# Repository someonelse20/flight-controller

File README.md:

# Custom Flight Controller

A custom flight controller with IMU sensors for orientation, a GPS module, a Micro SD card slot, and support for my LoRa Transceiver module for telemetry along with a custom flight controller algorithm.
I built this for my project of creating a custom drone from scratch. 

## Usage
To use plug in a 3 cell lipo battery into the XT60 connector and attach the ESCs to the 4 corner screw terminals. Then plug in the ESC headers into the coresponding ESC headers on the board. 
Make sure a GPS antenna is connected to the U.FL connector. Plug in my transceiver module into any of the UART headers.
A Micro SD card is not strictly required but if inserted the board will log data and error logs. 

## Project Images

## BOM
The full BOM from digikey is in the digikey-bom.csv file in production.

| PCB Assembly        | JLCPCB  | 96.10 | https://jlcpcb.com                                 |
|---------------------|---------|-------|----------------------------------------------------|
| Hand Soldered Parts | Digikey | 67.30 | https://www.digikey.com/en/mylists/list/OHMGL71TDV |

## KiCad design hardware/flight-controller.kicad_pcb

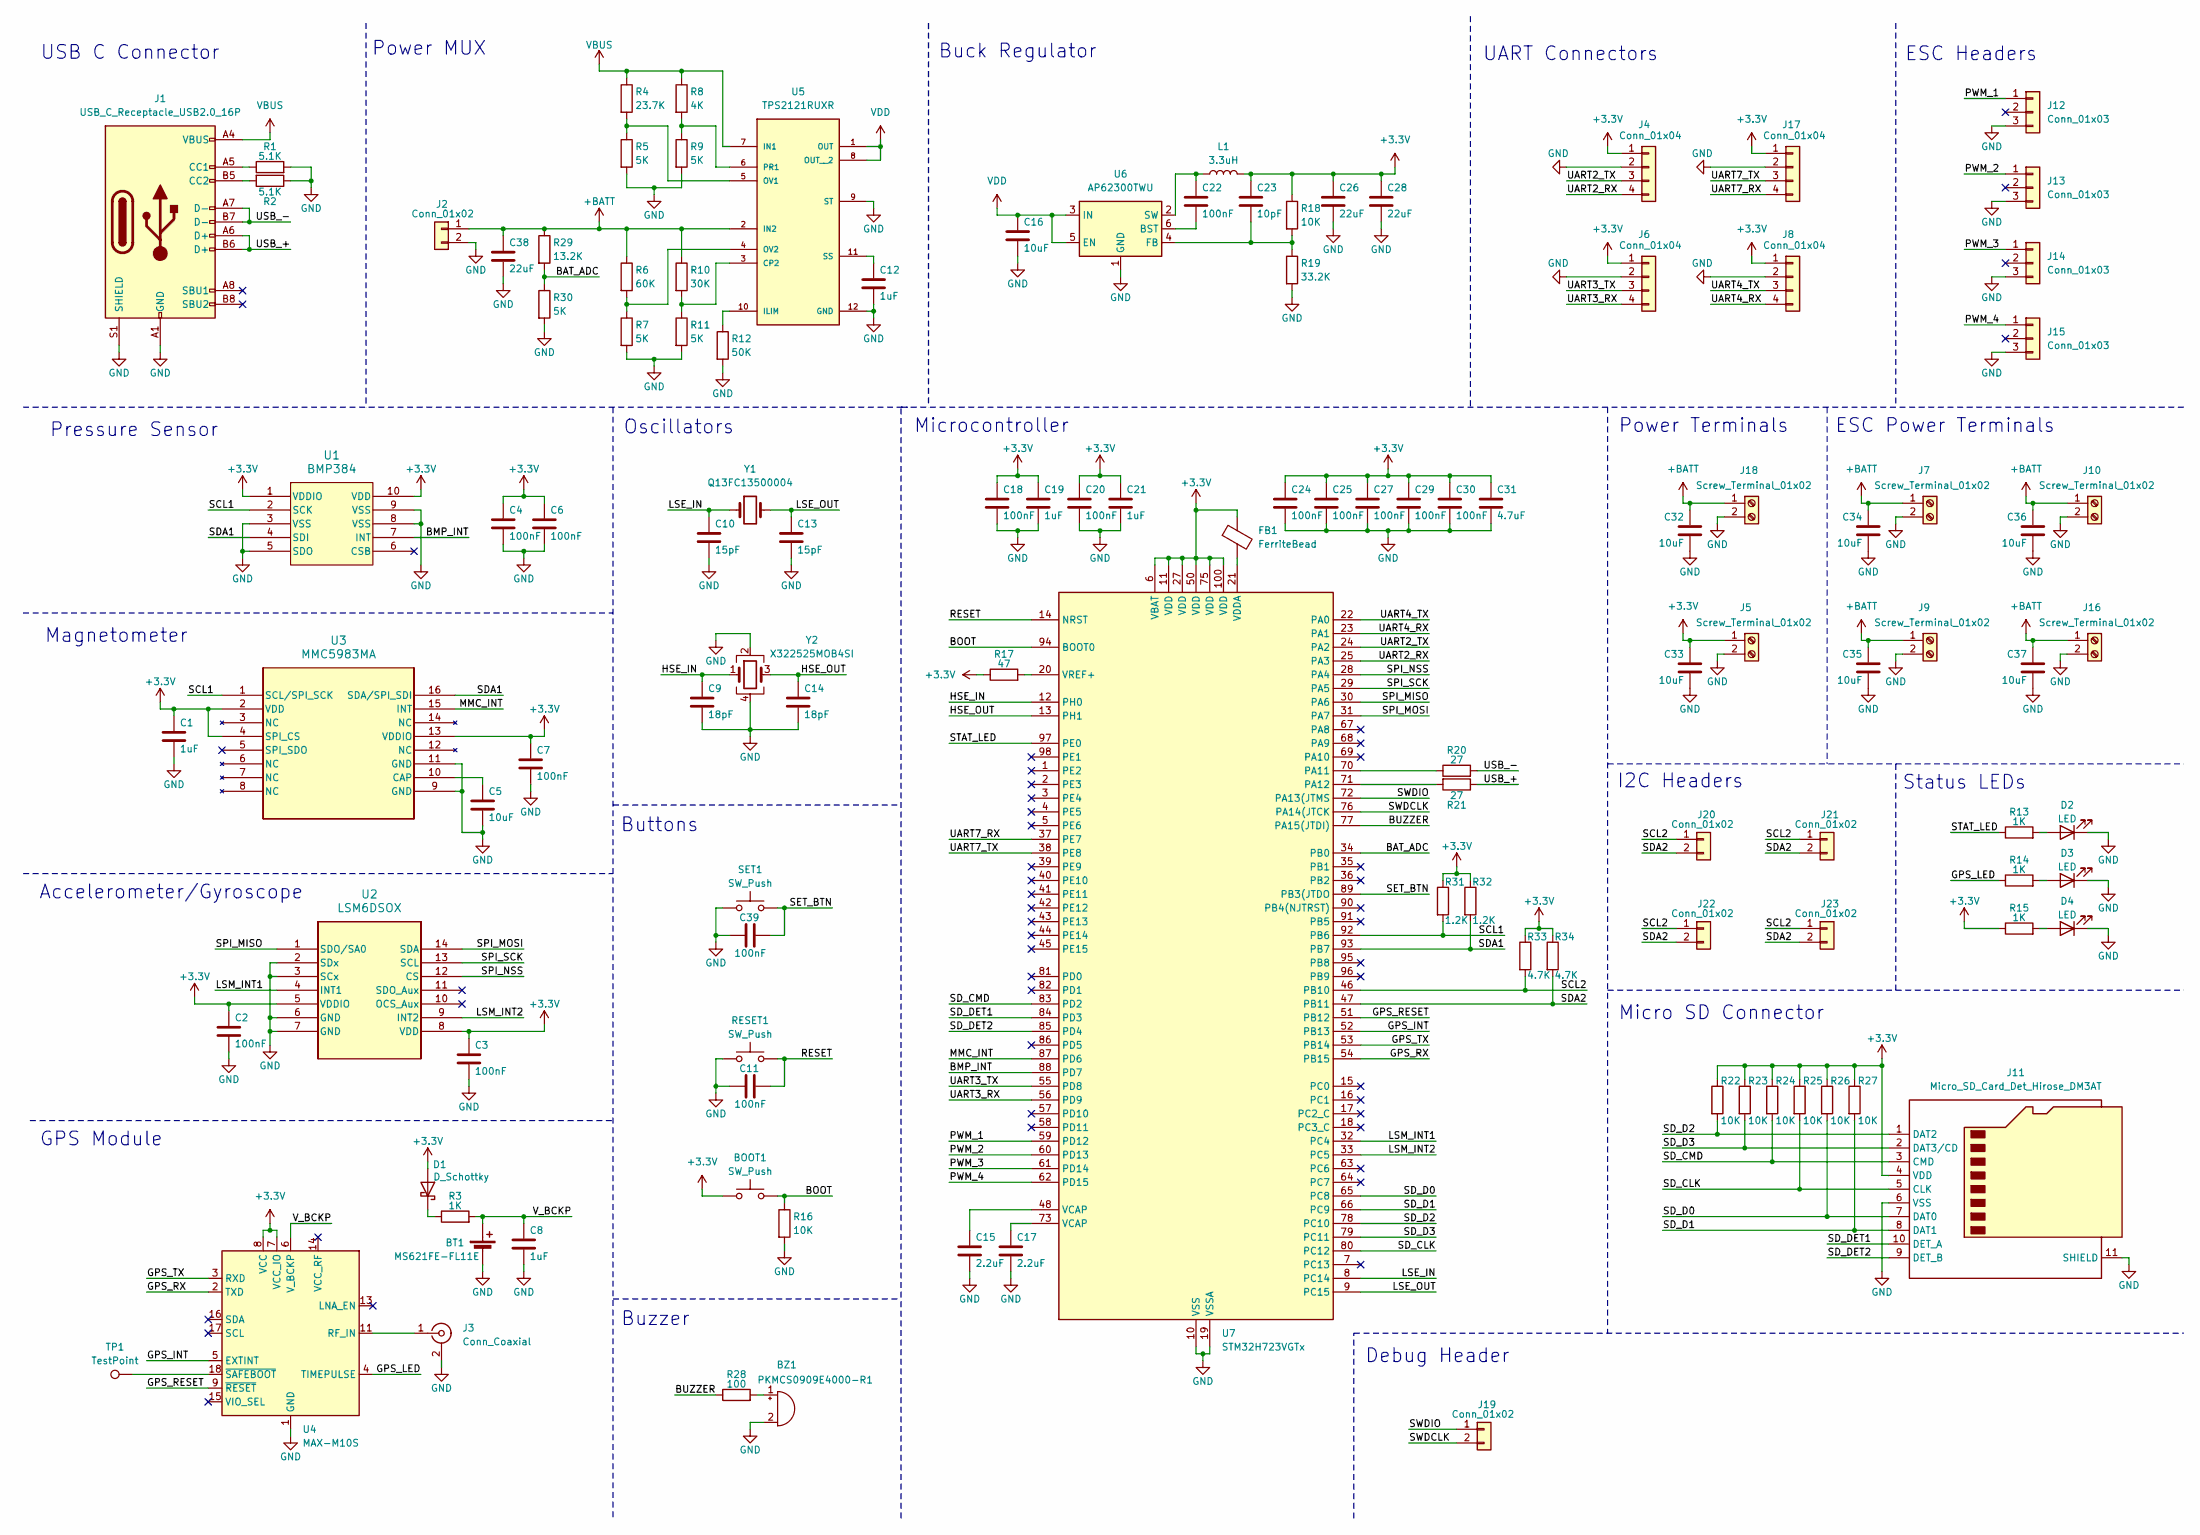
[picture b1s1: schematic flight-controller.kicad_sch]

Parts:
BOOT1: SW_Push; SW_Push_SPST_NO_Alps_SKRK
BT1: MS621FE-FL11E; BAT_MS621FE-FL11E
BZ1: PKMCS0909E4000-R1; SPKR_PKMCS0909E4000-R1
C1, C8, C19, C21: 1uF; C_0603_1608Metric
C2, C3, C4, C6, C7, C11, C18, C20, C22, C24, C25, C27, C29, C30, C39: 100nF; C_0402_1005Metric
C5, C16: 10uF; C_0603_1608Metric
C9, C14: 18pF; C_0402_1005Metric
C10, C13: 15pF; C_0402_1005Metric
C12: 1uF; C_0402_1005Metric
C15, C17: 2.2uF; C_0402_1005Metric
C23: 10pF; C_0402_1005Metric
C26, C28: 22uF; C_0603_1608Metric
C31: 4.7uF; C_0603_1608Metric
C32, C33, C34, C35, C36, C37: 10uF; C_0805_2012Metric
C38: 22uF; C_1206_3216Metric
D1: D_Schottky; D_0603_1608Metric
D2, D3, D4: LED; LED_0603_1608Metric
FB1: FerriteBead; L_0603_1608Metric
J1: USB_C_Receptacle_USB2.0_16P; USB_C_Receptacle_GCT_USB4105-xx-A_16P_TopMnt_Horizontal
J2: Conn_01x02; AMASS_XT60-M_1x02_P7.20mm_Vertical
J3: Conn_Coaxial; U.FL_Molex_MCRF_73412-0110_Vertical
J4, J6, J8, J17: Conn_01x04; JST_XH_B4B-XH-A_1x04_P2.50mm_Vertical
J5, J7, J9, J10, J16, J18: Screw_Terminal_01x02; TerminalBlock_MaiXu_MX126-5.0-02P_1x02_P5.00mm
J11: Micro_SD_Card_Det_Hirose_DM3AT; microSD_HC_Hirose_DM3AT-SF-PEJM5
J12, J13, J14, J15: Conn_01x03; PinHeader_1x03_P2.54mm_Vertical
J19, J20, J21, J22, J23: Conn_01x02; PinHeader_1x02_P2.54mm_Vertical
L1: 3.3uH; IND_SRP4030FA_BRN
R1, R2: 5.1K; R_0402_1005Metric
R3, R13, R14, R15: 1K; R_0402_1005Metric
R4: 23.7K; R_0402_1005Metric
R5, R7, R9, R11, R30: 5K; R_0402_1005Metric
R6: 60K; R_0603_1608Metric
R8: 4K; R_0603_1608Metric
R10: 30K; R_0402_1005Metric
R12: 50K; R_0603_1608Metric
R16, R18, R22, R23, R24, R25, R26, R27: 10K; R_0402_1005Metric
R17: 47; R_0402_1005Metric
R19: 33.2K; R_0402_1005Metric
R20, R21: 27; R_0402_1005Metric
R28: 100; R_0402_1005Metric
R29: 13.2K; R_0603_1608Metric
R31, R32: 1.2K; R_0603_1608Metric
R33, R34: 4.7K; R_0402_1005Metric
RESET1: SW_Push; SW_Push_SPST_NO_Alps_SKRK
SET1: SW_Push; SW_Push_SPST_NO_Alps_SKRK
TP1: TestPoint; TestPoint_Pad_D1.0mm
U1: BMP384; Rohm_MLGA010V020A_LGA-10_2x2mm_P0.45mm_LayoutBorder2x3y
U2: LSM6DSOX; LGA-14_3x2.5mm_P0.5mm_LayoutBorder3x4y
U3: MMC5983MA; LGA-16_3x3mm_P0.5mm
U4: MAX-M10S; ublox_MAX
U5: TPS2121RUXR; IC_TPS2121RUXR
U6: AP62300TWU; TSOT-23-6
U7: STM32H723VGTx; LQFP-100_14x14mm_P0.5mm
Y1: Q13FC13500004; Crystal_SMD_3215-2Pin_3.2x1.5mm
Y2: X322525MOB4SI; Crystal_SMD_3225-4Pin_3.2x2.5mm

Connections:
+3.3V: BOOT1.1, C1.1, C2.1, C3.1, C4.1, C6.1, C7.1, C18.1, C19.1, C20.1, C21.1, C23.1, C24.1, C25.1, C26.1, C27.1, C28.1, C29.1, C30.1, C31.1, C33.1, D1.2 (A), FB1.1, J4.1, J5.1, J6.1, J8.1, J11.4 (VDD), J17.1, L1.2, R15.1, R17.1, R18.1, R22.1, R23.1, R24.1, R25.1, R26.1, R27.1, R31.1, R32.1, R33.1, R34.1, U1.1 (VDDIO), U1.10 (VDD), U2.5 (VDDIO), U2.8 (VDD), U3.2 (VDD), U3.4 (SPI_CS), U3.13 (VDDIO), U4.7 (VCC_IO), U4.8 (VCC), U7.6 (VBAT), U7.11 (VDD), U7.27 (VDD), U7.50 (VDD), U7.75 (VDD), U7.100 (VDD); also elsewhere on the board
+BATT: C32.1, C34.1, C35.1, C36.1, C37.1, C38.1, J2.1, J7.1, J9.1, J10.1, J16.1, J18.1, R6.1, R10.1, R29.1, U5.2 (IN2)
/BAT_ADC: R29.2, R30.1, U7.34 (PB0)
/BMP_INT: U1.7 (INT), U7.88 (PD7)
/BOOT: BOOT1.2, R16.1, U7.94 (BOOT0)
/BUZZER: R28.1, U7.77 (PA15(JTDI))
/GPS_INT: U4.5 (EXTINT), U7.52 (PB13); also elsewhere on the board
/GPS_LED: R14.1, U4.4 (TIMEPULSE); also elsewhere on the board
/GPS_RESET: U4.9 (~RESET), U7.51 (PB12); also elsewhere on the board
/GPS_RX: U4.2 (TXD), U7.54 (PB15); also elsewhere on the board
/GPS_TX: U4.3 (RXD), U7.53 (PB14); also elsewhere on the board
/HSE_IN: C9.1, U7.12 (PH0), Y2.1
/HSE_OUT: C14.1, U7.13 (PH1), Y2.3
/LSE_IN: C10.1, U7.8 (PC14), Y1.1
/LSE_OUT: C13.1, U7.9 (PC15), Y1.2
/LSM_INT1: U2.4 (INT1), U7.32 (PC4)
/LSM_INT2: U2.9 (INT2), U7.33 (PC5)
/MMC_INT: U3.15 (INT), U7.87 (PD6)
/PWM_1: J12.1, U7.59 (PD12)
/PWM_2: J13.1, U7.60 (PD13)
/PWM_3: J14.1, U7.61 (PD14)
/PWM_4: J15.1, U7.62 (PD15)
/RESET: C11.2, RESET1.2, U7.14 (NRST)
/SCL1: R31.2, U1.2 (SCK), U3.1 (SCL/SPI_SCK), U7.92 (PB6)
/SCL2: J20.1, J21.1, J22.1, J23.1, R33.2, U7.46 (PB10)
/SDA1: R32.2, U1.4 (SDI), U3.16 (SDA/SPI_SDI), U7.93 (PB7)
/SDA2: J20.2, J21.2, J22.2, J23.2, R34.2, U7.47 (PB11)
/SD_CLK: J11.5 (CLK), R25.2, U7.80 (PC12)
/SD_CMD: J11.3 (CMD), R24.2, U7.83 (PD2)
/SD_D0: J11.7 (DAT0), R26.2, U7.65 (PC8)
/SD_D1: J11.8 (DAT1), R27.2, U7.66 (PC9)
/SD_D2: J11.1 (DAT2), R22.2, U7.78 (PC10)
/SD_D3: J11.2 (DAT3/CD), R23.2, U7.79 (PC11)
/SD_DET1: J11.10 (DET_A), U7.84 (PD3)
/SD_DET2: J11.9 (DET_B), U7.85 (PD4)
/SET_BTN: C39.2, SET1.2, U7.89 (PB3(JTDO)
/SPI_MISO: U2.1 (SDO/SA0), U7.30 (PA6)
/SPI_MOSI: U2.14 (SDA), U7.31 (PA7)
/SPI_NSS: U2.12 (CS), U7.28 (PA4)
/SPI_SCK: U2.13 (SCL), U7.29 (PA5)
/STAT_LED: R13.1, U7.97 (PE0)
/SWDCLK: J19.2, U7.76 (PA14(JTCK)
/SWDIO: J19.1, U7.72 (PA13(JTMS)
/UART2_RX: J4.4, U7.25 (PA3)
/UART2_TX: J4.3, U7.24 (PA2)
/UART3_RX: J6.4, U7.56 (PD9)
/UART3_TX: J6.3, U7.55 (PD8)
/UART4_RX: J8.4, U7.23 (PA1)
/UART4_TX: J8.3, U7.22 (PA0)
/UART7_RX: J17.4, U7.37 (PE7)
/UART7_TX: J17.3, U7.38 (PE8)
/USB_+: J1.A6 (D+), J1.B6 (D+), R21.1
/USB_-: J1.A7 (D-), J1.B7 (D-), R20.2
/V_BCKP: BT1.1 (+), C8.1, R3.2, U4.6 (V_BCKP); also elsewhere on the board
GND: BT1.2 (-), BZ1.2 (-), C1.2, C2.2, C3.2, C4.2, C5.2, C6.2, C7.2, C8.2, C9.2, C10.2, C11.1, C12.2, C13.2, C14.2, C15.2, C16.2, C17.2, C18.2, C19.2, C20.2, C21.2, C24.2, C25.2, C26.2, C27.2, C28.2, C29.2, C30.2, C31.2, C32.2, C33.2, C34.2, C35.2, C36.2, C37.2, C38.2, C39.1, D2.1 (K), D3.1 (K), D4.1 (K), J1.A1 (GND), J1.A12 (GND), J1.B1 (GND), J1.B12 (GND), J1.S1 (SHIELD), J2.2, J3.2 (Ext), J4.2, J5.2, J6.2, J7.2, J8.2, J9.2, J10.2, J11.6 (VSS), J11.11 (SHIELD), J12.3, J13.3, J14.3, J15.3, J16.2, J17.2, J18.2, R1.2, R2.1, R5.2, R7.2, R9.2, R11.2, R12.2, R16.2, R19.2, R30.2, RESET1.1, SET1.1, U1.3 (VSS), U1.5 (SDO), U1.8 (VSS), U1.9 (VSS), U2.2 (SDx), U2.3 (SCx), U2.6 (GND), U2.7 (GND), U3.9 (GND), U3.11 (GND), U4.1 (GND), U4.10 (GND), U4.12 (GND), U5.9 (ST), U5.12 (GND), U6.1 (GND), U7.10 (VSS), U7.19 (VSSA), U7.26 (VSS), U7.49 (VSS), U7.74 (VSS), U7.99 (VSS), Y2.2, Y2.4; also elsewhere on the board
unnamed: BZ1.1 (+), R28.2
unnamed: C15.1, U7.48 (VCAP)
unnamed: C17.1, U7.73 (VCAP)
unnamed: D1.1 (K), R3.1
unnamed: D2.2 (A), R13.2
unnamed: D3.2 (A), R14.2
unnamed: D4.2 (A), R15.2
unnamed: J1.A5 (CC1), R1.1
unnamed: J1.B5 (CC2), R2.2
unnamed 64: J3.1 (In), U4.11 (RF_IN); also elsewhere on the board
unnamed: C5.1, U3.10 (CAP)
unnamed: R10.2, R11.1, U5.3 (CP2)
unnamed: R12.1, U5.10 (ILIM)
unnamed: R4.2, R5.1, U5.5 (OV1)
unnamed: R6.2, R7.1, U5.4 (OV2)
unnamed: R8.2, R9.1, U5.6 (PR1)
unnamed: C12.1, U5.11 (SS)
unnamed: C22.2, U6.6 (BST)
unnamed: C23.2, R18.2, R19.1, U6.4 (FB)
unnamed: C22.1, L1.1, U6.2 (SW)
unnamed: R20.1, U7.70 (PA11)
unnamed: R21.2, U7.71 (PA12)
unnamed: FB1.2, U7.21 (VDDA)
unnamed: R17.2, U7.20 (VREF+)
unnamed 79: TP1.1, U4.18 (~SAFEBOOT); also elsewhere on the board
VBUS: J1.A4 (VBUS), J1.A9 (VBUS), J1.B4 (VBUS), J1.B9 (VBUS), R4.1, R8.1, U5.7 (IN1)
VDD: C16.1, U5.1 (OUT), U5.8 (OUT__2), U6.3 (IN), U6.5 (EN)

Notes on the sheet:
Microcontroller
Micro SD Connector
Power MUX
Status LEDs
Magnetometer
Oscillators
Buzzer
ESC Power Terminals
Accelerometer/Gyroscope
Buttons
UART Connectors
ESC Headers
Pressure Sensor
Debug Header
Buck Regulator
Power Terminals
I2C Headers
USB C Connector
GPS Module

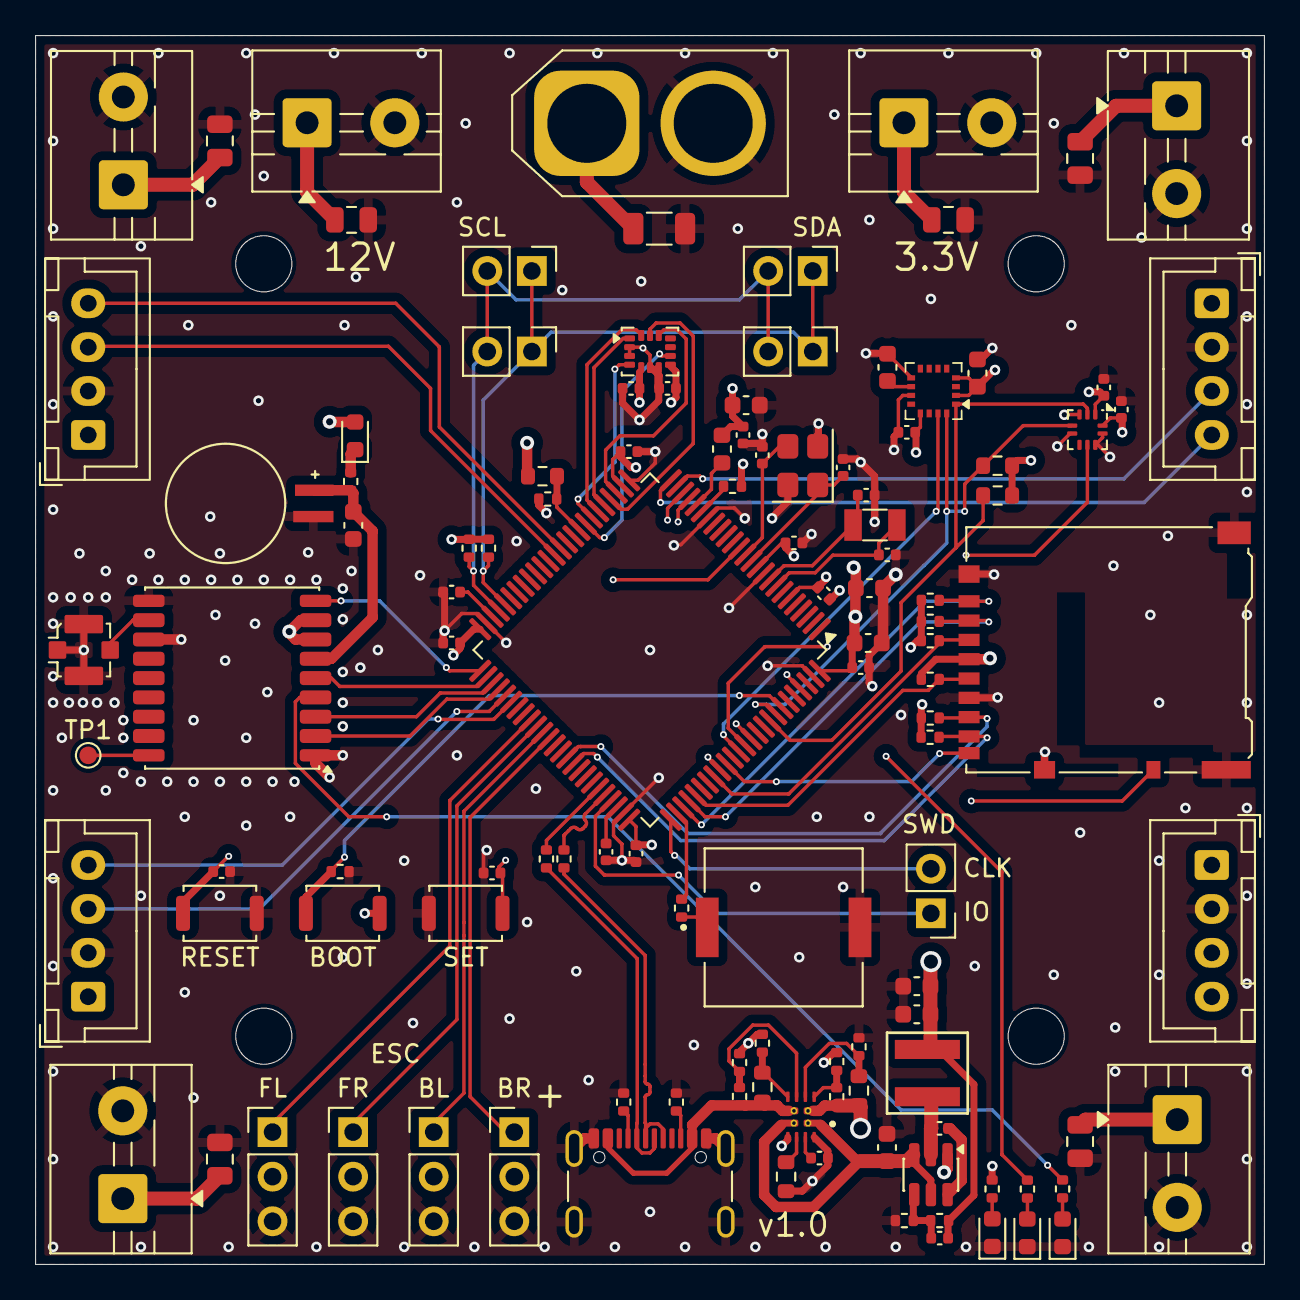
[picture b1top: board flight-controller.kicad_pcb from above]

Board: 4 copper layers, 70.0 x 70.0 mm, 117 parts (0 on the bottom side), 82 nets.

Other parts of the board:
U8: MAX-M10S; ublox_MAX

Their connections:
+3.3V: U8.7 (VCC_IO), U8.8 (VCC); also elsewhere on the board
/GPS_INT: U8.5 (EXTINT); also elsewhere on the board
/GPS_LED: U8.4 (TIMEPULSE); also elsewhere on the board
/GPS_RESET: U8.9 (~RESET); also elsewhere on the board
/GPS_RX: U8.2 (TXD); also elsewhere on the board
/GPS_TX: U8.3 (RXD); also elsewhere on the board
/V_BCKP: U8.6 (V_BCKP); also elsewhere on the board
GND: U8.1 (GND), U8.10 (GND), U8.12 (GND); also elsewhere on the board
unnamed 64: U8.11 (RF_IN); also elsewhere on the board
unnamed 79: U8.18 (~SAFEBOOT); also elsewhere on the board

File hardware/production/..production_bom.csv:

Designator,Footprint,Quantity,Value,LCSC Part #
"BOOT1, RESET1, SET1",SW_Push_SPST_NO_Alps_SKRK,3,SW_Push,
BT1,BAT_MS621FE-FL11E,1,MS621FE-FL11E,
BZ1,SPKR_PKMCS0909E4000-R1,1,PKMCS0909E4000-R1,
"C1, C19, C21, C8",0603,4,1uF,
"C10, C13",0402,2,15pF,
"C11, C18, C2, C20, C22, C24, C25, C27, C29, C3, C30, C39, C4, C6, C7",0402,15,100nF,
C12,0402,1,1uF,
"C14, C9",0402,2,18pF,
"C15, C17",0402,2,2.2uF,
"C16, C5",0603,2,10uF,
C23,0402,1,10pF,
"C26, C28",0603,2,22uF,
C31,0603,1,4.7uF,
"C32, C33, C34, C35, C36, C37",0805,6,10uF,
C38,1206,1,22uF,
D1,0603,1,D_Schottky,
"D2, D3, D4",0603,3,LED,
FB1,0603,1,FerriteBead,
J1,USB_C_Receptacle_GCT_USB4105-xx-A_16P_TopMnt_Horizontal,1,USB_C_Receptacle_USB2.0_16P,
"J10, J16, J18, J5, J7, J9",TerminalBlock_MaiXu_MX126-5.0-02P_1x02_P5.00mm,6,Screw_Terminal_01x02,
J11,microSD_HC_Hirose_DM3AT-SF-PEJM5,1,Micro_SD_Card_Det_Hirose_DM3AT,
"J12, J13, J14, J15",PinHeader_1x03_P2.54mm_Vertical,4,Conn_01x03,
"J17, J4, J6, J8",JST_XH_B4B-XH-A_1x04_P2.50mm_Vertical,4,Conn_01x04,
"J19, J20, J21, J22, J23",PinHeader_1x02_P2.54mm_Vertical,5,Conn_01x02,
J2,AMASS_XT60-M_1x02_P7.20mm_Vertical,1,Conn_01x02,
J3,U.FL_Molex_MCRF_73412-0110_Vertical,1,Conn_Coaxial,
L1,IND_SRP4030FA_BRN,1,3.3uH,
"R1, R2",0402,2,5.1K,
R10,0402,1,30K,
"R11, R30, R5, R7, R9",0402,5,5K,
R12,0603,1,50K,
"R13, R14, R15, R3",0402,4,1K,
"R16, R18, R22, R23, R24, R25, R26, R27",0402,8,10K,
R17,0402,1,47,
R19,0402,1,33.2K,
"R20, R21",0402,2,27,
R28,0402,1,100,
R29,0603,1,13.2K,
"R31, R32",0603,2,1.2K,
"R33, R34",0402,2,4.7K,
R4,0402,1,23.7K,
R6,0603,1,60K,
R8,0603,1,4K,
TP1,TestPoint_Pad_D1.0mm,1,TestPoint,
U1,Rohm_MLGA010V020A_LGA-10_2x2mm_P0.45mm_LayoutBorder2x3y,1,BMP384,
U2,LGA-14_3x2.5mm_P0.5mm_LayoutBorder3x4y,1,LSM6DSOTR,
U3,LGA-16_3x3mm_P0.5mm,1,MMC5983MA,
U4,ublox_NEO,1,NEO-M9N,
U5,IC_TPS2121RUXR,1,TPS2121RUXR,
U6,TSOT-23-6,1,AP62300TWU,
U7,LQFP-100_14x14mm_P0.5mm,1,STM32H723VGTx,
Y1,Crystal_SMD_3215-2Pin_3.2x1.5mm,1,Q13FC13500004,
Y2,Crystal_SMD_3225-4Pin_3.2x2.5mm,1,X322525MOB4SI,

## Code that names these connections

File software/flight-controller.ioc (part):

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Mcu.Name=STM32H723VGTx
Mcu.Package=LQFP100
Mcu.UserName=STM32H723VGTx
PA0.Mode=Asynchronous
PA0.Signal=UART4_TX
PA1.Mode=Asynchronous
PA1.Signal=UART4_RX
PA11.Mode=Device_Only_FS
PA11.Signal=USB_OTG_HS_DM
PA12.Mode=Device_Only_FS
PA12.Signal=USB_OTG_HS_DP
PA13(JTMS/SWDIO).Mode=Serial_Wire
PA13(JTMS/SWDIO).Signal=DEBUG_JTMS-SWDIO
PA14(JTCK/SWCLK).Mode=Serial_Wire
PA14(JTCK/SWCLK).Signal=DEBUG_JTCK-SWCLK
PA15(JTDI).Signal=GPIO_Output
PA2.Mode=Asynchronous
PA2.Signal=USART2_TX
PA3.Mode=Asynchronous
PA3.Signal=USART2_RX
PA4.Mode=NSS_Signal_Hard_Output
PA4.Signal=SPI1_NSS
PA5.Mode=Full_Duplex_Master
PA5.Signal=SPI1_SCK
PA6.Mode=Full_Duplex_Master
PA6.Signal=SPI1_MISO
PA7.Mode=Full_Duplex_Master
PA7.Signal=SPI1_MOSI
PB0.Signal=ADCx_INP9
PB10.Mode=I2C
PB10.Signal=I2C2_SCL
PB11.Mode=I2C
PB11.Signal=I2C2_SDA
PB12.Signal=GPIO_Output
PB13.Signal=EVENTOUT
PB14.Mode=Asynchronous
PB14.Signal=USART1_TX
PB15.Mode=Asynchronous
PB15.Signal=USART1_RX
PB3(JTDO/TRACESWO).Signal=GPIO_Input
PB6.Mode=I2C
PB6.Signal=I2C1_SCL
PB7.Mode=I2C
PB7.Signal=I2C1_SDA
PC10.Mode=SD_4_bits_Wide_bus
PC10.Signal=SDMMC1_D2
PC11.Mode=SD_4_bits_Wide_bus
PC11.Signal=SDMMC1_D3
PC12.Mode=SD_4_bits_Wide_bus
PC12.Signal=SDMMC1_CK
PC14-OSC32_IN.Mode=LSE-External-Oscillator
PC14-OSC32_IN.Signal=RCC_OSC32_IN
PC15-OSC32_OUT.Mode=LSE-External-Oscillator
PC15-OSC32_OUT.Signal=RCC_OSC32_OUT
PC4.Signal=GPXTI4
PC5.Signal=GPXTI5
PC8.Mode=SD_4_bits_Wide_bus
PC8.Signal=SDMMC1_D0
PC9.Mode=SD_4_bits_Wide_bus
PC9.Signal=SDMMC1_D1
PD12.Signal=S_TIM4_CH1
PD13.Signal=S_TIM4_CH2
PD14.Signal=S_TIM4_CH3
PD15.Signal=S_TIM4_CH4
PD2.Mode=SD_4_bits_Wide_bus
PD2.Signal=SDMMC1_CMD
PD3.Signal=GPIO_Input
PD4.Signal=GPIO_Input
PD6.Signal=GPXTI6
PD7.Signal=GPXTI7
PD8.Mode=Asynchronous
PD8.Signal=USART3_TX
PD9.Mode=Asynchronous
PD9.Signal=USART3_RX
PE0.Signal=GPIO_Output
PE7.Mode=Asynchronous
PE7.Signal=UART7_RX
PE8.Mode=Asynchronous
PE8.Signal=UART7_TX
PH0-OSC_IN.Mode=HSE-External-Oscillator
PH0-OSC_IN.Signal=RCC_OSC_IN
PH1-OSC_OUT.Mode=HSE-External-Oscillator
PH1-OSC_OUT.Signal=RCC_OSC_OUT
RCC.SYSCLKFreq_VALUE=64000000
board=custom

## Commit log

2026-03-02 started schematic
2026-03-03 made schematic outline
2026-03-03 configured firmware
2026-03-03 added gps
2026-03-06 worked on schematic
2026-03-07 routed schematic
2026-03-09 worked on layout
2026-03-09 added uart port and buzzer
2026-03-10 routing pcb
2026-03-10 added buzzer type
2026-03-10 isolated magnetometer
2026-03-10 added untracked files
2026-03-10 finished pcb
2026-03-10 added 3d files
2026-03-10 finished board
2026-03-11 added I2C pins
2026-03-11 rewriting ahrs lib
2026-03-11 added seperate I2C channel
2026-03-11 added pwm silkscreen
2026-03-12 rewrote ahrs to c
2026-03-12 fixed usb plug
2026-03-12 added pid lib
2026-03-12 cleaning up
2026-03-12 fixed kicad error
2026-03-13 updated silkscreen
2026-03-13 added lsm6dso lib
2026-03-13 changed int pins and fixed i2c
2026-03-14 added mag driver
2026-03-14 moved int pins
2026-03-14 added pressure sensor driver
2026-03-14 added gnss driver
2026-03-14 updated .gitmodules
2026-03-14 fixed gps
2026-03-14 added sd card and basic error handling
2026-03-14 added base controll alg
2026-03-16 added i2c pullup resistors
2026-03-16 added transceiver support
2026-03-16 added assets
2026-03-16 added lines to schematic
2026-03-17 added production files
2026-03-17 replaced gps with max-m10s
2026-03-17 updated production files
2026-03-17 touching up pcb
2026-03-18 added silkscreen
2026-03-18 updated pcb
2026-03-18 added step file
